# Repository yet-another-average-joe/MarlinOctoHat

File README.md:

# MarlinOctoHat
 
How to get rid of the Reprap Discount Full Graphics Smart Controller, and display Marlin on the OctoPi LCD.

The easiest and most efficient way to fetch the Marlin UI frames is to enable the MKS_12864OLED display in Configuration.h.

The MKS OLED 1.3" 128x64 Full Graphics Controller is based on the SSD1306, a very common OLED module. This display basically is an SPI slave. But the RaspBerry Foundation didn't think or didn't want to enable/support the SPI slave mode, which is required for emulation....

The Marlin graphics driver (a optimized u8glib fork) sends bitmaps @1Mbps. The STM32 BluePill gets these frames, reencodes them, and makes them available to the RaspBerry Pi SPI master interface. When a new frame is ready, the STM32 sends a pulse to the RasPi. The RasPi then reads the STM32 at up to 28Mbps (adjustable in the OctoPrint plugin).

As a result, the printer motherboard "sees" a SSD1306 SPI slave, and the RasPi "sees" the printer motherboard as a SPI slave peripheral ! Thanks to the STM32F103 dual SPI, and to the developpers that implemented the SPI DMA mode in the Roger's core !

The RaspBerry runs a service that overlays the Marlin UI onto the RaspBerry display using dispmanx, and an OctoPrint plugin allows for easy display customization.

This repo contains everything needed to build the hat (two PCBs and a firmware) that replaces the 12864 display. The hat is connected to the printer motherboard through the EXP1 and EXP2 connectors, and breaks out the rotary encoder, the reset button for the STM32 and the motherboard, the speaker, the "Marlin Mode" button, and a 5V screw terminal to for the RasPi and the STM32 power. It also breaks out the RasPi UART for direct connection to the motherboard (if supported...). Both 3.3V and 5V printer motherboards are supported.

The two PCBs are inexpensive, easy to populate using a decent soldering iron, and require components that every tinkerer has at hand (through hole only) : a BluePill (legit or fake), a couple of NPN tranistors and resistors, a small diode, 4 jumpers and some pinheaders and sockets (including a long RaspBerry 2x20 PC104-style pin header/socket). Everything can be easily sourced from Amazon, eBay, Ali...

The KiCad projects and the Gerber files are provided. Just order the PCBs from a manufacturer (JLCPCB, PCBWay, etc.)

Hat firmware : see https://github.com/yet-another-average-joe/MarlinOctoHat/tree/main/MarlinOctoHat_Firmware

RasPi software (service and OctoPrint plugin) :

service : https://github.com/yet-another-average-joe/OctoPrint_MarlinOSD_Service

plugin : https://github.com/yet-another-average-joe/OctoPrint_MarlinOSD_Plugin

**The SSD1306 (MKS OLED 1.3" 128x64 Full Graphics Controller) is not supported for all motherboards, even though the option is available in Configuration.h ; enabling support is not difficult, but requires sone basic knowledge about Marlin and microcontrollers ! The pins files are somewhere under Marlin/src/pins : some "#define..." to add if needed. The motherboard schematics and pinouts might be needed ; forums and dicussion groups could be helpfull !**

First, enable the "MKS OLED 1.3" 128x64 Full Graphics Controller" in Configurattion.h :

#define MKS_12864OLED

If the OLED is not supported, you will get a compile error similar to :

In file included from Marlin\src\lcd\dogm\marlinui_DOGM.cpp:42:

Marlin\src\lcd\dogm\marlinui_DOGM.cpp: In static member function 'static void MarlinUI::init_lcd()':

Marlin\src\lcd\dogm\marlinui_DOGM.h:223:48: error: 'DOGLCD_CS' was not declared in this scope; did you mean 'DOGLCD_SCK'?

You'll have to add such a block in your pins definition file :

      #elif ENABLED(MKS_12864OLED_SSD1306)
        #define DOGLCD_CS            EXP1_05_PIN
        #define DOGLCD_A0            EXP1_04_PIN
        #define DOGLCD_SCK           EXP2_09_PIN
        #define DOGLCD_MOSI          EXP2_05_PIN
        #define LCD_PINS_DC          LCD_PINS_D4
        //#define FORCE_SOFT_SPI                      // Use this if default of hardware SPI causes display problems
      #endif

You could have to figure wich microcontroller pins go to the EXP1 and EXP2 pin headers. May be done without the schematics, but easier with.

**THIS IS AN EXAMPLE !** : lines I had to add to /Marlin/src/pins/lpc1768/pins_BTT_SKR_V1_4.h for a SKR 1.4 Turbo.

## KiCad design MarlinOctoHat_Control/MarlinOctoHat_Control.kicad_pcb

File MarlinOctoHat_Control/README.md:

# MarlinOctoHat_Control : control board
 
**KiCad 6.0 project** :

subfolders :

- **bom** : bill of material created with "Interactive Html Bom" plugin
- **fabrication** : fabrication files created with "KiCAD JLCPCB tools" plugin

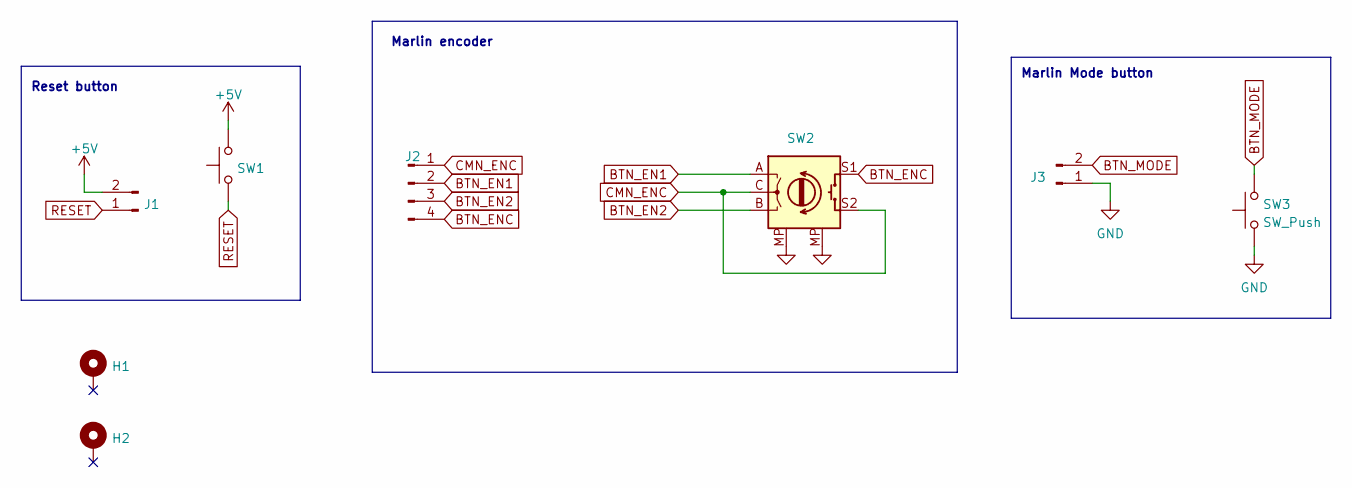
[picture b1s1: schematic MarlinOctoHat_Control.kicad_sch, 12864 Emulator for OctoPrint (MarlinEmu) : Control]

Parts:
H1, H2: MountingHole; MountingHole_3.2mm_M3_Pad_Via
J1, J3: Conn_01x02_Male; JST_KNOCKOFF_XH_B2B-XH-A_1x02_P2.54mm_Vertical
J2: Conn_01x04_Male; JST_KNOCKOFF_XH_B4B-XH-A_1x04_P2.54mm_Vertical
SW1, SW3: SW_Push; SW_PUSH_6mm_H4.3mm_Orig_Center
SW2: RotaryEncoder_Switch; RotaryEncoder_Alps_EC11E-Switch_Vertical_H20mm_CircularMoun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

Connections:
+5V: J1.2, SW1.2
BTN_EN1: J2.2, SW2.A
BTN_EN2: J2.3, SW2.B
BTN_ENC: J2.4, SW2.S1
BTN_MODE: J3.2, SW3.2
CMN_ENC: J2.1, SW2.C, SW2.S2
GND: J3.1, SW2.MP, SW3.1
RESET: J1.1, SW1.1

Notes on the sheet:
Marlin Mode button
Reset button
Marlin encoder

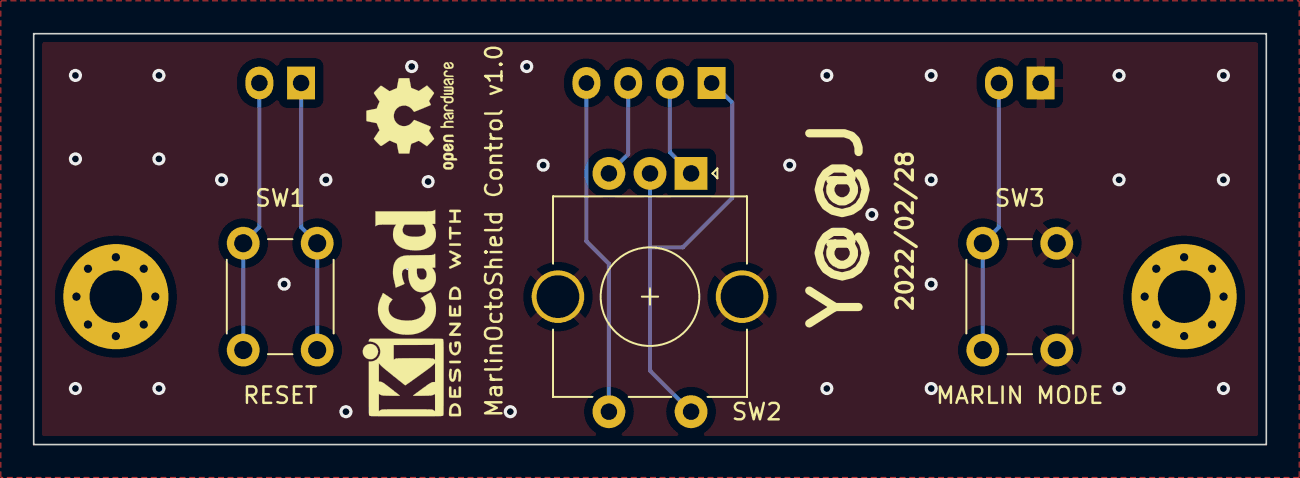
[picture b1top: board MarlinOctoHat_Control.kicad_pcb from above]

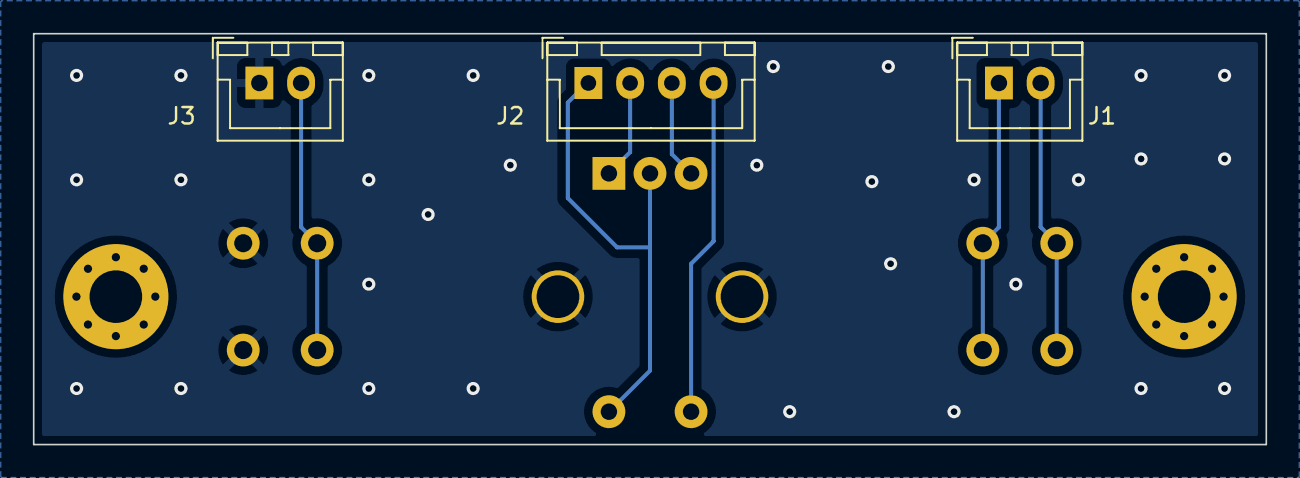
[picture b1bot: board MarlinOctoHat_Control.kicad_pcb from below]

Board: 2 copper layers, 75.0 x 25.0 mm, 8 parts (3 on the bottom side), 8 nets.

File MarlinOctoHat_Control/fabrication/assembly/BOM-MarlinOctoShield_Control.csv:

Comment,Designator,Footprint,LCSC
SW_Push,SW1,SW_PUSH_6mm_H4.3mm_Orig_Center,
MountingHole,H2,MountingHole_3.2mm_M3_Pad_Via,
MountingHole,H1,MountingHole_3.2mm_M3_Pad_Via,
RotaryEncoder_Switch,SW2,RotaryEncoder_Alps_EC11E-Switch_Vertical_H20mm_CircularMountingHoles_Orig_Center,
3,SW3,SW_PUSH_6mm_H4.3mm_Orig_Center,
Conn_01x02_Male,J3,JST_KNOCKOFF_XH_B2B-XH-A_1x02_P2.54mm_Vertical,
Conn_01x04_Male,J2,JST_KNOCKOFF_XH_B4B-XH-A_1x04_P2.54mm_Vertical,
Conn_01x02_Male,J1,JST_KNOCKOFF_XH_B2B-XH-A_1x02_P2.54mm_Vertical,

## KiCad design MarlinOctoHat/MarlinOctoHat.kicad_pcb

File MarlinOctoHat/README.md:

# MarlinOctoHat : hat PCB
 
The Blue Pill may be legit or "fake" : tested with ST Microeletronics STM32F103C8 and chinese CKS32F103C8T6.

**KiCad 6.0 project** :

subfolders :

- **bom** : bill of material created with "Interactive Html Bom" plugin
- **fabrication** : fabrication files created with "KiCAD JLCPCB tools" plugin

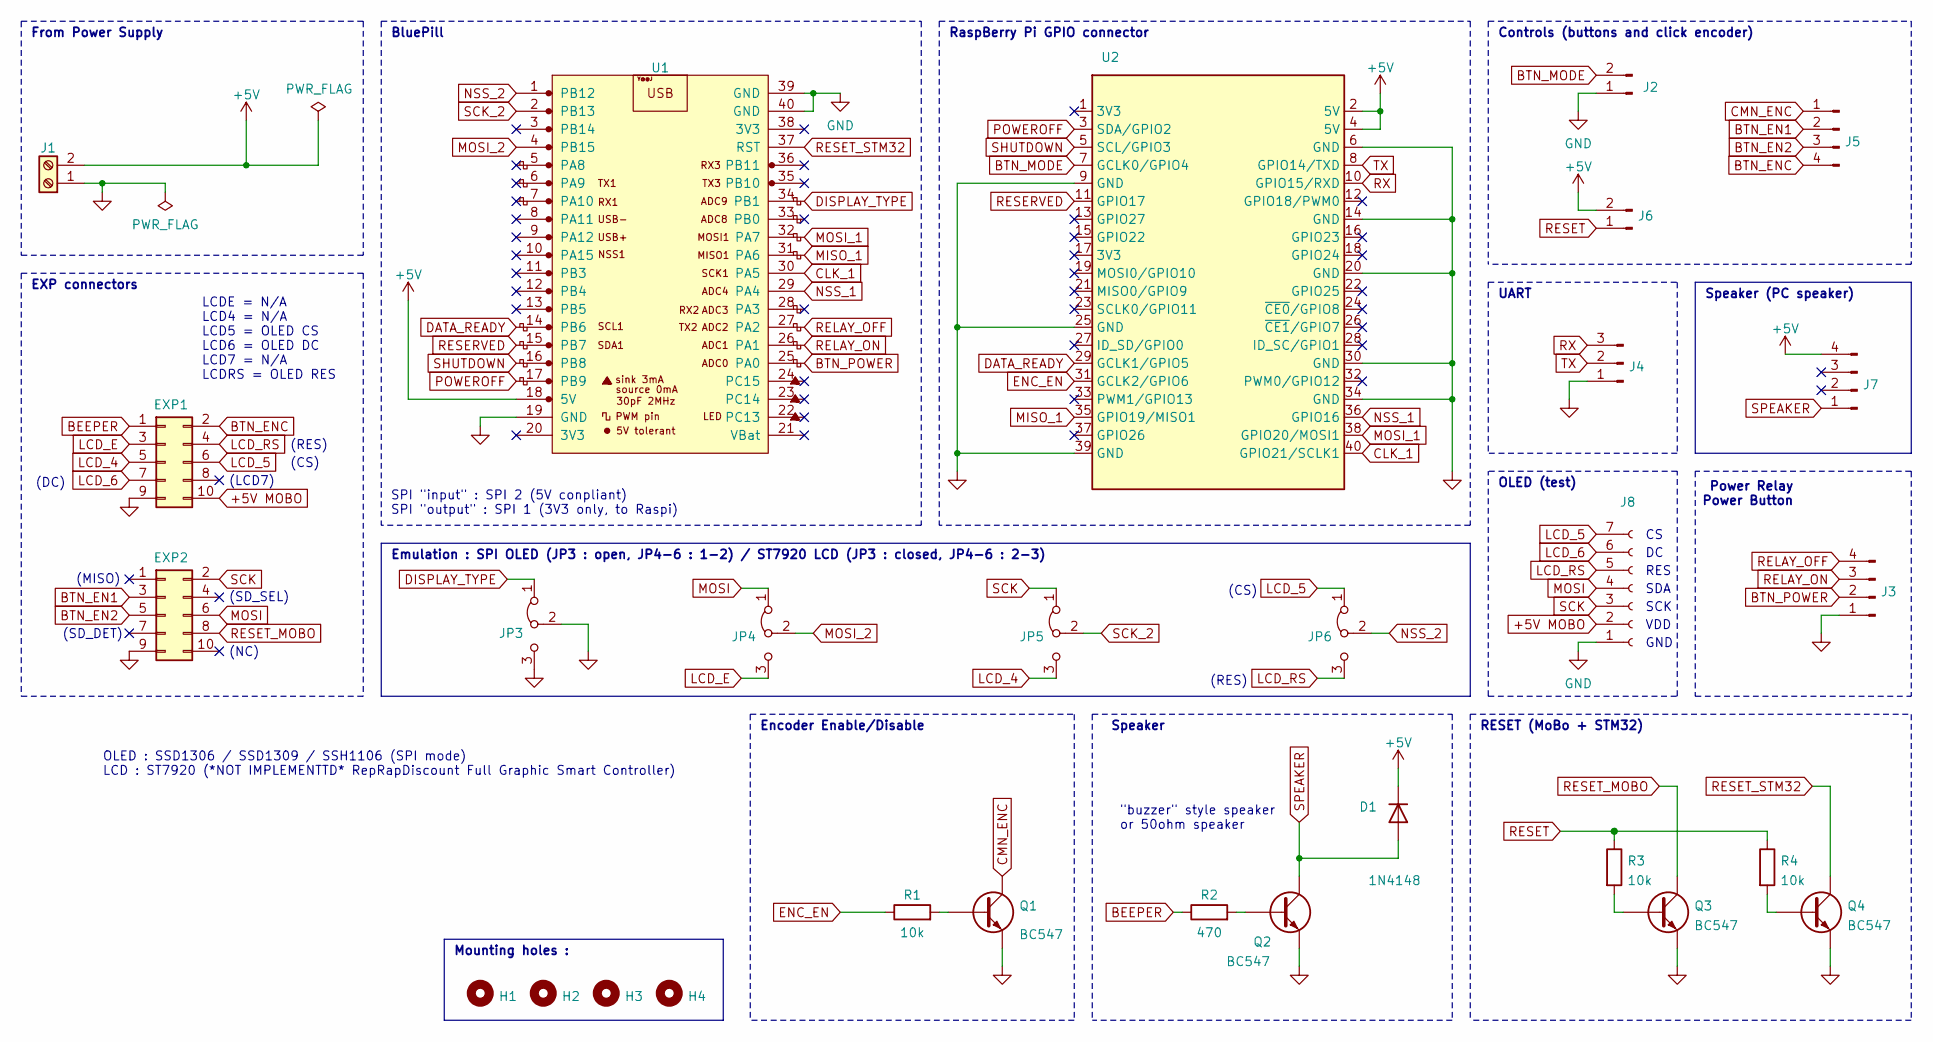
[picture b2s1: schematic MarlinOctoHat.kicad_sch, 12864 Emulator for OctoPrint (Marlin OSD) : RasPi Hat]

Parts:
D1: 1N4148; D_DO-35_SOD27_P7.62mm_Horizontal
EXP1, EXP2: Conn_02x05_Odd_Even; IDC-Header_2x05_P2.54mm_Vertical
H1, H2, H3, H4: MountingHole; MountingHole_2.7mm_M2.5_DIN965
J1: Screw_Terminal_01x03; TerminalBlock_Phoenix_MKDS-1,5-2-5.08_1x02_P5.08mm_Horizont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
J2, J6: Conn_01x02_Male; JST_KNOCKOFF_XH_B2B-XH-A_1x02_P2.54mm_Vertical
J3, J5: Conn_01x04_Male; JST_KNOCKOFF_XH_B4B-XH-A_1x04_P2.54mm_Vertical
J4: Conn_01x03_Male; JST_KNOCKOFF_XH_B3B-XH-A_1x03_P2.54mm_Vertical
J7: Conn_01x04_Male; PinHeader_1x04_P2.54mm_Vertical
J8: Conn_01x07_Female; PinSocket_1x07_P2.54mm_Vertical
JP3: Jumper_2_Open; PinHeader_1x03_P2.54mm_Vertical
JP4, JP5, JP6: Jumper_3_Bridged12; PinHeader_1x03_P2.54mm_Vertical
Q1, Q2, Q3, Q4: BC547; TO-92_Inline
R1, R3, R4: 10k; R_Axial_DIN0207_L6.3mm_D2.5mm_P7.62mm_Horizontal
R2: 470; R_Axial_DIN0207_L6.3mm_D2.5mm_P7.62mm_Horizontal
U1: YAAJ_BluePill_Part_Like; YAAJ_BluePill_1
U2: YAAJ_Raspberry_Pi_2_3_GPIO; PinHeader_2x20_P2.54mm_Vertical

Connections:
+5V: D1.1 (K), J1.2, J6.2, J7.4, U1.18 (5V), U2.2 (5V), U2.4 (5V)
+5V MOBO: EXP1.10, J8.2
BEEPER: EXP1.1, R2.1
BTN_EN1: EXP2.3, J5.2
BTN_EN2: EXP2.5, J5.3
BTN_ENC: EXP1.2, J5.4
BTN_MODE: J2.2, U2.7 (GCLK0/GPIO4)
BTN_POWER: J3.2, U1.25 (PA0)
CLK_1: U1.30 (PA5), U2.40 (GPIO21/SCLK1)
CMN_ENC: J5.1, Q1.1 (C)
DATA_READY: U1.14 (PB6), U2.29 (GCLK1/GPIO5)
DISPLAY_TYPE: JP3.1 (A), U1.34 (PB1)
ENC_EN: R1.1, U2.31 (GCLK2/GPIO6)
GND: EXP1.9, EXP2.9, J1.1, J2.1, J3.1, J4.1, J8.1, JP3.2 (C), JP3.3 (B), Q1.3 (E), Q2.3 (E), Q3.3 (E), Q4.3 (E), U1.19 (GND), U1.39 (GND), U1.40 (GND), U2.6 (GND), U2.9 (GND), U2.14 (GND), U2.20 (GND), U2.25 (GND), U2.30 (GND), U2.34 (GND), U2.39 (GND)
LCD_4: EXP1.5, JP5.3 (B)
LCD_5: EXP1.6, J8.7, JP6.1 (A)
LCD_6: EXP1.7, J8.6
LCD_E: EXP1.3, JP4.3 (B)
LCD_RS: EXP1.4, J8.5, JP6.3 (B)
MISO_1: U1.31 (PA6), U2.35 (GPIO19/MISO1)
MOSI: EXP2.6, J8.4, JP4.1 (A)
MOSI_1: U1.32 (PA7), U2.38 (GPIO20/MOSI1)
MOSI_2: JP4.2 (C), U1.4 (PB15)
NSS_1: U1.29 (PA4), U2.36 (GPIO16)
NSS_2: JP6.2 (C), U1.1 (PB12)
unnamed: Q1.2 (B), R1.2
unnamed: Q2.2 (B), R2.2
unnamed: Q3.2 (B), R3.2
unnamed: Q4.2 (B), R4.2
POWEROFF: U1.17 (PB9), U2.3 (SDA/GPIO2)
RELAY_OFF: J3.4, U1.27 (PA2)
RELAY_ON: J3.3, U1.26 (PA1)
RESERVED: U1.15 (PB7), U2.11 (GPIO17)
RESET: J6.1, R3.1, R4.1
RESET_MOBO: EXP2.8, Q3.1 (C)
RESET_STM32: Q4.1 (C), U1.37 (RST)
RX: J4.3, U2.10 (GPIO15/RXD)
SCK: EXP2.2, J8.3, JP5.1 (A)
SCK_2: JP5.2 (C), U1.2 (PB13)
SHUTDOWN: U1.16 (PB8), U2.5 (SCL/GPIO3)
SPEAKER: D1.2 (A), J7.1, Q2.1 (C)
TX: J4.2, U2.8 (GPIO14/TXD)

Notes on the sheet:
OLED (test)
SCK
(LCD7)
OLED : SSD1306 / SSD1309 / SSH1106 (SPI mode) LCD : ST7920 (*NOT IMPLEMENTTD* RepRapDiscount Full Graphic Smart Controller)
RaspBerry Pi GPIO connector
Emulation : SPI OLED (JP3 : open, JP4-6 : 1-2) / ST7920 LCD (JP3 : closed, JP4-6 : 2-3)
(NC)
(CS)
GND
UART
BluePill
(SD_SEL)
RESET (MoBo + STM32)
(DC)
From Power Supply
Speaker (PC speaker)
Mounting holes :
(SD_DET)
RES
VDD
SDA
SPI "input" : SPI 2 (5V conpliant) SPI "output" : SPI 1 (3V3 only, to Raspi)
"buzzer" style speaker or 50ohm speaker
(RES)
Speaker
Encoder Enable/Disable
EXP connectors
Power Relay Power Button
(MISO)
Controls (buttons and click encoder)
LCDE = N/A LCD4 = N/A LCD5 = OLED CS LCD6 = OLED DC LCD7 = N/A LCDRS = OLED RES

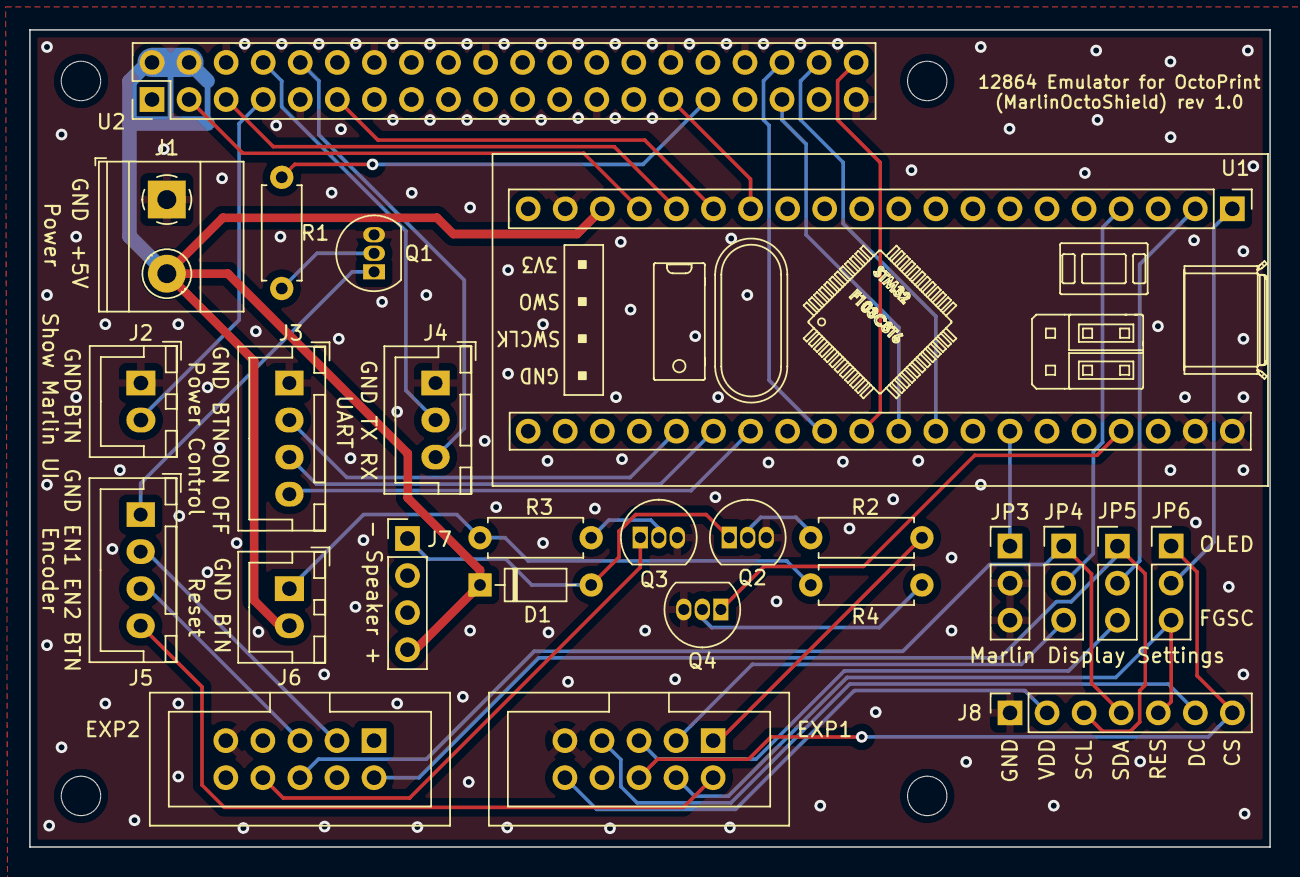
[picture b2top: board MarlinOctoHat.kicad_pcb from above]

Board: 2 copper layers, 85.0 x 56.0 mm, 30 parts (1 on the bottom side), 42 nets.

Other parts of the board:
LOGO1: OSHW-Logo_7.5x8mm_SilkScreen

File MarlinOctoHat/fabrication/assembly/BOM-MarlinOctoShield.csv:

Comment,Designator,Footprint,LCSC
BC547,Q3,TO-92_Inline,
Jumper_3_Bridged12,JP6,PinHeader_1x03_P2.54mm_Vertical,
10k,R1,R_Axial_DIN0207_L6.3mm_D2.5mm_P7.62mm_Horizontal,
BC547,Q4,TO-92_Inline,
MountingHole,H1,MountingHole_2.7mm_M2.5_DIN965,
MountingHole,H4,MountingHole_2.7mm_M2.5_DIN965,
Conn_01x02_Male,J2,JST_KNOCKOFF_XH_B2B-XH-A_1x02_P2.54mm_Vertical,
Jumper_2_Open,JP3,PinHeader_1x03_P2.54mm_Vertical,
Jumper_3_Bridged12,JP4,PinHeader_1x03_P2.54mm_Vertical,
Conn_01x02_Male,J6,JST_KNOCKOFF_XH_B2B-XH-A_1x02_P2.54mm_Vertical,
Conn_01x07_Female,J8,PinSocket_1x07_P2.54mm_Vertical,
MountingHole,H2,MountingHole_2.7mm_M2.5_DIN965,
YAAJ_BluePill_Part_Like,U1,YAAJ_BluePill_1,
Conn_02x05_Odd_Even,EXP1,IDC-Header_2x05_P2.54mm_Vertical,
Conn_01x04_Male,J3,JST_KNOCKOFF_XH_B4B-XH-A_1x04_P2.54mm_Vertical,
Conn_01x03_Male,J4,JST_KNOCKOFF_XH_B3B-XH-A_1x03_P2.54mm_Vertical,
BC547,Q2,TO-92_Inline,
Screw_Terminal_01x03,J1,"TerminalBlock_Phoenix_MKDS-1,5-2-5.08_1x02_P5.08mm_Horizontal",
1N4148,D1,D_DO-35_SOD27_P7.62mm_Horizontal,
Jumper_3_Bridged12,JP5,PinHeader_1x03_P2.54mm_Vertical,
MountingHole,H3,MountingHole_2.7mm_M2.5_DIN965,
10k,R4,R_Axial_DIN0207_L6.3mm_D2.5mm_P7.62mm_Horizontal,
Conn_02x05_Odd_Even,EXP2,IDC-Header_2x05_P2.54mm_Vertical,
10k,R3,R_Axial_DIN0207_L6.3mm_D2.5mm_P7.62mm_Horizontal,
Conn_01x02_Male,J7,PinHeader_1x04_P2.54mm_Vertical,
Conn_01x04_Male,J5,JST_KNOCKOFF_XH_B4B-XH-A_1x04_P2.54mm_Vertical,
YAAJ_Raspberry_Pi_2_3_GPIO,U2,PinHeader_2x20_P2.54mm_Vertical,
470,R2,R_Axial_DIN0207_L6.3mm_D2.5mm_P7.62mm_Horizontal,
BC547,Q1,TO-92_Inline,

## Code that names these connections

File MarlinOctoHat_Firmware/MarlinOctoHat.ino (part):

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 Created:    31/08/2021 11:16:18
 Author:    Y@@J
    TODO : pins PB10/PB11 = input for emulator selection OLED SSD1306 / OLED SSD1309 / OLED SSH1106 / LCD ST7920
            DISPLAY_TYPE : PB1
    TODO : power management
            support for monostable relay throught PIN_RELAY_ON
    /////////////////////////////////////////////////////////////////////////////////////
    SPI Slave Sniffer for the SSD1306/SSD1309/SSH1106 OLED ; for marlin UI, u8glib
    tested Ok with SPI SSD1309 OLED and Marlin v2.0.x on genuine and fake STM32F103C6 ("BluePill")
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    DC : LOW for commands only
    // BluePill / RaspBerry Pi wirings
                                              ----------
                        (LCD_5)  [NSS2] PB12 |            | GND
                        (SCK)    [SCK2] PB13 |            | GND
                                        PB14 |            | 3V3
                        (MOSI)  [MOSI2] PB15 |            | RESET
                                         PA8 |            | PB11 -> GPIO2  (AUX4)
                                         PA9 |            | PB10 -> GPIO3  (AUX3)
                                        PA10 |            | PB1
                                        PA11 |            | PB0
                                        PA12 |            | PA7  [MOSI1] -> GPIO20 (SPI1 MOSI)
                                        PA15 |            | PA6  [MISO1] -> GPIO19 (SPI1 MISO)
                             (LCD_E)    PB3  |            | PA5  [SCK1]  -> GPIO21 (SPI1 SCLK)
                             (LCD_4)    PB4  |            | PA4  [NSS1]  -> GPIO16 (SPI1 CS0)
                             (LCD_7)    PB5  |            | PA3
        GPIO5  <- DATA_READY            PB6  |            | PA2  PIN_RELAY_OFF
        GPIO17 <- PIN_SOFT_SHUTDOWN     PB7  |            | PA1  PIN_RELAY_ON
        GPIO3  <- PIN_HARD_SHUTDOWN     PB8  |            | PA0  PIN_BTN_POWER
        GPIO2  <- PIN_POWEROFF          PB9  |            | PC15
                                         5V  |            | PC14
                                        GND  |            | PC13
                                        3V3  |            | VBAT
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    ---------------------------------------------------
        STM32 Pins : 5V tolerant
            MoBo        OLED    BluePill
            XP1_5        CS        PB12    PIN_SS_2
            XP2-9        SCL       PB13    PIN_SCK_2
                         N/C       PB14
            EXP2-5       SDA       PB15    PIN_MOSI_2
    SPI1 :    SPI "output" (MISO), to RasPi
    -------------------------------------
        STM32 Pins : /!\ NOT 5V TOLERANT /!\
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                        tells the RasPi it's time to get data and refresh display
                        drastically reduces RasPi CPU usage
                    BluePill            PasPi
             PA7    PIN_MOSI1            [38]    GPIO20    MOSI1
            (PA6    PIN_MISO1            [35]    GPIO19    MISO1)
             PA5    PIN_SCK1             [40]    GPIO21    SCK1
             PA4    PIN_NSS1             [36]    GPIO16    NSS1
             PB6    PIN_READY            [29]    GPIO5     data ready to send
             PB7    PIN_SOFT_SHUTDOWN    [11]    GPIO17    output, default = LOW, HIGH = short press -> OctoPrint Shutdown
             PB8    PIN_HARD_SHUTDOWN    [5]     GPIO3     output, default = LOW, HIGH triggered by PIN_BTN_POWER long press -> OS Shutdown
             PB9    PIN_POWEROFF         [3]     GPIO2     input, interrupt
             PA0    PIN_BTN_POWER        [33]    GPIO13    input, pullup,    interrupt, sends 1 sec LOW pulse to PIN_HARD_SHUTDOWN
             PA1    PIN_RELAY_ON         [32]    GPIO12    output, default = LOW, HIGH for 1 sec at boot
             PA2    PIN_RELAY_OFF        [31]    GPIO6     output, default = LOW, HIGH triggerd by PIN_POWEROFF

*/
lkjhsqdgfklhjgbqskdhjgbksdqjhgdksjhkqgqsdkjfhgqsdf
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
#define READY_PULSE_DURATION    1        // 1ms

#define PIN_READY        PB6

//#define PIN_HARD_SHUTDOWN    PB8        // to RasPi Shutdown pin (5 / GPIO3)
//#define PIN_POWEROFF         PB9        // from RasPi PowerOff pin (2 / GPIO2)
#define PIN_BTN_POWER        PA0        // Power button
#define PIN_RELAY_ON         PA1        // to PSU module ; ON bistable coil
#define PIN_RELAY_OFF        PA2        // to PSU module ; OFF bistable coil
#define PIN_SOFT_SHUTDOWN    PB7        // to RasPi (11 / GPIO17)

#define LONG_PRESS_TIME            1500    // milliseconds
#define DEBOUNCE_TIME                25    // milliseconds
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
SPIClass SPI_2(2);

#define PIN_NSS_2    PB12

volatile uint8_t SPI_2_Rx_Buffer[OLED_SPI_FRAME_SIZE] = { 0 };
volatile bool SPI_2_DMA_transfer_complete = false;
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}

//////////////////////////////////////////////////////////////////////////////////////////////////////////////
// ISR : PIN_POWEROFF
// "poweroff" from RasPi

bool flagPowerOff = false;
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
    pinMode(PIN_READY, OUTPUT);
    digitalWrite(PIN_READY, LOW);
    pinMode(PIN_NSS_2, INPUT);    // needed ?

    //pinMode(PIN_POWEROFF, INPUT);
    pinMode(PIN_BTN_POWER, INPUT_PULLUP);
    pinMode(PIN_RELAY_ON, OUTPUT);
    pinMode(PIN_RELAY_OFF, OUTPUT);

    // turn bistable relay on
    digitalWrite(PIN_RELAY_OFF, LOW);
    digitalWrite(PIN_RELAY_ON, HIGH);
    delay(RELAY_PULSE); // bistable relay pulse
    digitalWrite(PIN_RELAY_ON, LOW);

    attachInterrupt(digitalPinToInterrupt(PIN_NSS_2), ISR_NSS_2, RISING);
    //attachInterrupt(digitalPinToInterrupt(PIN_POWEROFF), ISR_POWEROFF, FALLING);

    setup_SPI_1();
    setup_SPI_1_DMA();
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#ifdef __SERIAL_DEBUG
        Serial.println("POWER OFF");
#endif
        //detachInterrupt(PIN_POWEROFF); // 2 falling edges ; ignore the second one
        //digitalWrite(PIN_RELAY_OFF, HIGH);
        //flagPowerOff = false; // otherwise : will be called until power is off
        // no further processing : power is now off...
    }
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    static uint32 btnState;
    static uint32 prevBtnState = HIGH;
    static bool done = false;
    //digitalWrite(PIN_HARD_SHUTDOWN, digitalRead(PIN_BTN_POWER));
    digitalWrite(PIN_SOFT_SHUTDOWN, digitalRead(PIN_BTN_POWER));
/*
    btnState = digitalRead(PIN_BTN_POWER);

    if (btnState == LOW && prevBtnState == HIGH && (millis() - firstButtonPressTime) > DEBOUNCE_TIME)
        firstButtonPressTime = millis();
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
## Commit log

2022-04-29 images
2022-05-09 25% faster matrix tranposition (gain = 1 millisecond)
2022-05-24 removed old firmware
